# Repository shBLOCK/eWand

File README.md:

# ⚡eWand: a smart portable electrostatic charge generator

**This project is still highly WIP, as of right now, it does generate charge, but not much control is possible yet.**
<br>
This project is a group project, deriving from my school's project-based learning month.
<br>
Documentation is WIP.

## ⚙️Main features
- Portable
- Fully solid-state operation
- Precisely controllable output
- Output charge measurement (WIP)
- Wireless connectivity
  - Remote configuration & control
  - Data feedback

## Usages
- Physics teaching aid
- ESD testing
- ...

## Notes
- This project is inspired by [Join The Technicians's device](https://www.youtube.com/watch?v=TUDd5lzepgE), but adds more "smart" features to make it more useful as a teaching aid device and for other purposes.

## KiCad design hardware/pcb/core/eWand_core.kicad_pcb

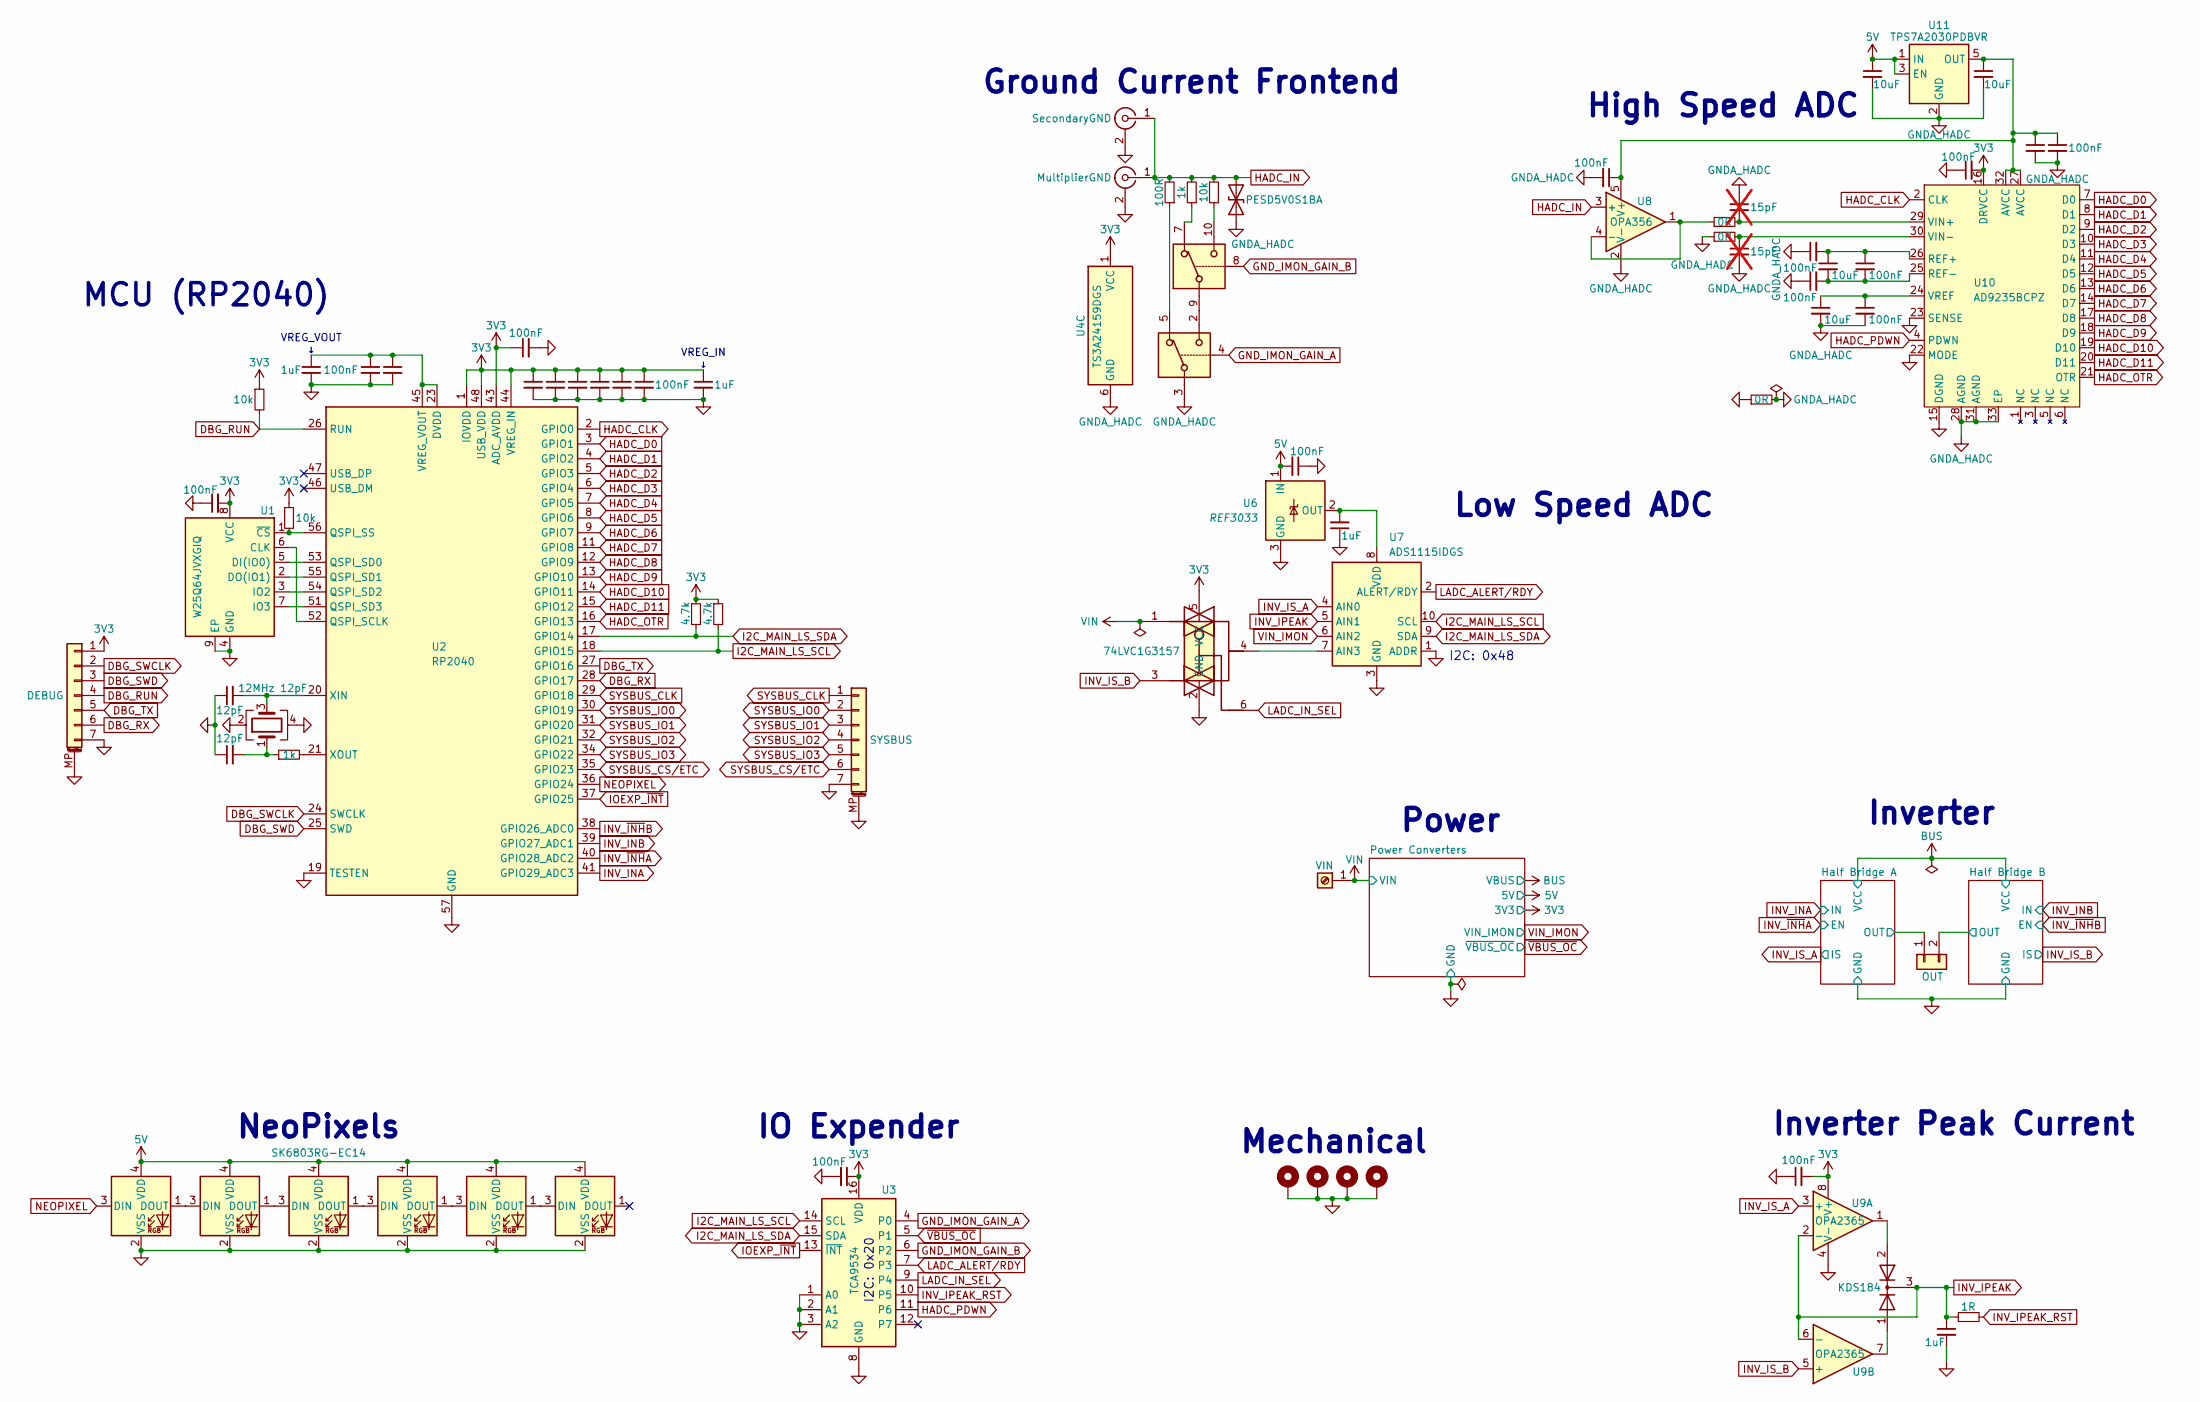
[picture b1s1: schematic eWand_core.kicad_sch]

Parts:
C1, C5, C6, C7, C8, C9, C10, C11, C12, C13, C15, C16, C18, C21, C22, C23, C26, C27, C30, C32, C33: 100nF; C_0402_1005Metric; LCSC C307331
C2, C3: 12pF; C_0402_1005Metric; LCSC C1547
C4, C14, C17: 1uF; C_0402_1005Metric; LCSC C52923
C19, C20: 15pF; C_0402_1005Metric; LCSC C1548; not fitted
C24, C25, C28, C31: 10uF; C_0402_1005Metric; LCSC C15525
C29: 1uF; C_0805_2012Metric; LCSC C28323
D1, D2, D3, D4, D5, D6: SK6803RG-EC14; LED_SK6812_EC15_1.5x1.5mm; LCSC C18548258
D7: PESD5V0S1BA; D_SOD-323; LCSC C19224
D8: KDS184; SOT-23; LCSC C112694
H1, H2, H3, H4: MountingHole_Pad; MountingHole_2.2mm_M2_Pad_Via
J1: DEBUG; TE_0-1734839-7_1x07-1MP_P0.5mm_Horizontal; LCSC C2911879
J2: SYSBUS; TE_0-1734839-7_1x07-1MP_P0.5mm_Horizontal; LCSC C262232
J3: SecondaryGND; U.FL_Molex_MCRF_73412-0110_Vertical; LCSC C411563
J4: MultiplierGND; U.FL_Molex_MCRF_73412-0110_Vertical; LCSC C411563
J5: VIN; T31000; LCSC C481468
J6: OUT; VH3.96-2AW; LCSC C722831
R1, R2: 10k; R_0402_1005Metric; LCSC C25744
R3: 1k; R_0402_1005Metric; LCSC C11702
R4, R5: 4.7k; R_0402_1005Metric; LCSC C25900
R6: 100R; C_0603_1608Metric; LCSC C22775
R7: 1k; C_0603_1608Metric; LCSC C21190
R8: 10k; C_0603_1608Metric; LCSC C25804
R9, R10: 0R; R_0402_1005Metric; LCSC C17168
R11: 0R; R_0603_1608Metric; LCSC C21189
R12: 1R; R_0402_1005Metric; LCSC C185446
U1: W25Q64JVXGIQ; WSON-8-1EP_4x4mm_P0.8mm_EP2.2x3mm; LCSC C2940195
U2: RP2040; QFN-56-1EP_7x7mm_P0.4mm_EP3.2x3.2mm; LCSC C2040
U3: TCA9534; TSSOP-16_4.4x5mm_P0.65mm; LCSC C206010
U4: TS3A24159DGS; TSSOP-10_3x3mm_P0.5mm; LCSC C129329
U5: 74LVC1G3157; SOT-363_SC-70-6; LCSC C38663
U6: REF3033; SOT-23; LCSC C36658
U7: ADS1115IDGS; TSSOP-10_3x3mm_P0.5mm; LCSC C37593
U8: OPA356; SOT-23-5; LCSC C183100
U9: OPA2365; SOIC-8_3.9x4.9mm_P1.27mm; LCSC C130011
U10: AD9235BCPZ; LFCSP-32-1EP_5x5mm_P0.5mm_EP3.1x3.1mm; LCSC C653330
U11: TPS7A2030PDBVR; SOT-23-5; LCSC C963429
Y1: 12MHz 12pF; Crystal_SMD_3225-4Pin_3.2x2.5mm; LCSC C70565

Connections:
3V3: C1.2, C7.1, C8.1, C9.1, C10.1, C11.1, C12.1, C13.1, C14.1, C15.1, C21.2, C30.2, J1.1, R1.1, R2.1, R4.1, R5.1, U1.8 (VCC), U2.1 (IOVDD), U2.10 (IOVDD), U2.22 (IOVDD), U2.33 (IOVDD), U2.42 (IOVDD), U2.43 (ADC_AVDD), U2.44 (VREG_IN), U2.48 (USB_VDD), U2.49 (IOVDD), U3.16 (VDD), U4.1 (VCC), U5.5 (VCC), U9.8 (V+), U10.16 (DRVCC); also elsewhere on the board
5V: C16.2, C28.1, D1.4 (VDD), D2.4 (VDD), D3.4 (VDD), D4.4 (VDD), D5.4 (VDD), D6.4 (VDD), U6.1 (IN), U11.1 (IN), U11.3 (EN); also elsewhere on the board
/Half Bridge A/OUT: J6.1; also elsewhere on the board
/Half Bridge B/OUT: J6.2; also elsewhere on the board
DBG_RUN: J1.4, R1.2, U2.26 (RUN)
DBG_RX: J1.6, U2.28 (GPIO17)
DBG_SWCLK: J1.2, U2.24 (SWCLK)
DBG_SWD: J1.3, U2.25 (SWD)
DBG_TX: J1.5, U2.27 (GPIO16)
GND: C1.1, C2.1, C3.1, C4.2, C5.2, C6.2, C7.2, C8.2, C9.2, C10.2, C11.2, C12.2, C13.2, C14.2, C15.2, C16.1, C17.1, C21.1, C29.2, C30.1, D1.2 (VSS), D2.2 (VSS), D3.2 (VSS), D4.2 (VSS), D5.2 (VSS), D6.2 (VSS), H1.1, H2.1, H3.1, H4.1, J1.7, J1.MP (MountPin), J2.7, J2.MP (MountPin), J3.2 (Ext), J4.2 (Ext), R11.1, U1.4 (GND), U1.9 (EP), U2.19 (TESTEN), U2.57 (GND), U3.1 (A0), U3.2 (A1), U3.3 (A2), U3.8 (GND), U5.2 (GND), U6.3 (GND), U7.1 (ADDR), U7.3 (GND), U9.4 (V-), U10.15 (DGND), U10.22 (MODE), U10.23 (SENSE), Y1.2, Y1.4; also elsewhere on the board
GNDA_HADC: C18.2, C19.1, C20.2, C22.1, C23.1, C24.2, C27.2, C28.2, C31.2, C32.2, C33.2, D7.1 (A1), R10.1, R11.2, U4.3, U4.6 (GND), U8.2 (V-), U10.28 (AGND), U10.31 (AGND), U10.33 (EP), U11.2 (GND)
GND_IMON_GAIN_A: U3.4 (P0), U4.4
GND_IMON_GAIN_B: U3.6 (P2), U4.8
HADC_CLK: U2.2 (GPIO0), U10.2 (CLK)
HADC_D0: U2.3 (GPIO1), U10.7 (D0)
HADC_D1: U2.4 (GPIO2), U10.8 (D1)
HADC_D2: U2.5 (GPIO3), U10.9 (D2)
HADC_D3: U2.6 (GPIO4), U10.10 (D3)
HADC_D4: U2.7 (GPIO5), U10.11 (D4)
HADC_D5: U2.8 (GPIO6), U10.12 (D5)
HADC_D6: U2.9 (GPIO7), U10.13 (D6)
HADC_D7: U2.11 (GPIO8), U10.14 (D7)
HADC_D8: U2.12 (GPIO9), U10.17 (D8)
HADC_D9: U2.13 (GPIO10), U10.18 (D9)
HADC_D10: U2.14 (GPIO11), U10.19 (D10)
HADC_D11: U2.15 (GPIO12), U10.20 (D11)
HADC_IN: D7.2 (A2), J3.1 (In), J4.1 (In), R6.2, R7.2, R8.2, U8.3 (+)
HADC_OTR: U2.16 (GPIO13), U10.21 (OTR)
HADC_PDWN: U3.11 (P6), U10.4 (PDWN)
I2C_MAIN_LS_SCL: R5.2, U2.18 (GPIO15), U3.14 (SCL), U7.10 (SCL); also elsewhere on the board
I2C_MAIN_LS_SDA: R4.2, U2.17 (GPIO14), U3.15 (SDA), U7.9 (SDA); also elsewhere on the board
INV_INA: U2.41 (GPIO29_ADC3); also elsewhere on the board
INV_INB: U2.39 (GPIO27_ADC1); also elsewhere on the board
INV_IPEAK: C29.1, D8.3 (K), R12.1, U7.5 (AIN1), U9.2 (-), U9.6 (-)
INV_IPEAK_RST: R12.2, U3.10 (P5)
INV_IS_A: U7.4 (AIN0), U9.3 (+); also elsewhere on the board
INV_IS_B: U5.3, U9.5 (+); also elsewhere on the board
INV_~INHA: U2.40 (GPIO28_ADC2); also elsewhere on the board
INV_~INHB: U2.38 (GPIO26_ADC0); also elsewhere on the board
IOEXP_~INT: U2.37 (GPIO25), U3.13 (~INT)
LADC_ALERT/RDY: U3.7 (P3), U7.2 (ALERT/RDY)
LADC_IN_SEL: U3.9 (P4), U5.6
NEOPIXEL: D1.3 (DIN), U2.36 (GPIO24)
unnamed: C3.2, R3.1, Y1.1
unnamed: D1.1 (DOUT), D2.3 (DIN)
unnamed: D2.1 (DOUT), D3.3 (DIN)
unnamed: D3.1 (DOUT), D4.3 (DIN)
unnamed: D4.1 (DOUT), D5.3 (DIN)
unnamed: D5.1 (DOUT), D6.3 (DIN)
unnamed: D8.1 (A), U9.7
unnamed: D8.2 (A), U9.1
unnamed: R6.1, U4.5
unnamed: R7.1, U4.7
unnamed: R8.1, U4.10
unnamed: U1.6 (CLK), U2.52 (QSPI_SCLK)
unnamed: U1.5 (DI(IO0)), U2.53 (QSPI_SD0)
unnamed: U1.2 (DO(IO1)), U2.55 (QSPI_SD1)
unnamed: U1.3 (IO2), U2.54 (QSPI_SD2)
unnamed: U1.7 (IO3), U2.51 (QSPI_SD3)
unnamed: R2.2, U1.1 (~CS), U2.56 (QSPI_SS)
unnamed: C4.1, C5.1, C6.1, U2.23 (DVDD), U2.45 (VREG_VOUT), U2.50 (DVDD)
unnamed: C2.2, U2.20 (XIN), Y1.3
unnamed: R3.2, U2.21 (XOUT)
unnamed: U4.2, U4.9
unnamed: C17.2, U6.2 (OUT), U7.8 (VDD)
unnamed: U5.4, U7.7 (AIN3)
unnamed: R9.1, U8.1, U8.4 (-)
unnamed: C22.2, C25.1, C26.1, U10.26 (REF+)
unnamed: C23.2, C25.2, C26.2, U10.25 (REF-)
unnamed: C19.2, R9.2, U10.29 (VIN+)
unnamed: C20.1, R10.2, U10.30 (VIN-)
unnamed: C24.1, C27.1, U10.24 (VREF)
unnamed: C18.1, C31.1, C32.1, C33.1, U8.5 (V+), U10.27 (AVCC), U10.32 (AVCC), U11.5 (OUT)
SYSBUS_CLK: J2.1, U2.29 (GPIO18)
SYSBUS_CS/ETC: J2.6, U2.35 (GPIO23)
SYSBUS_IO0: J2.2, U2.30 (GPIO19)
SYSBUS_IO1: J2.3, U2.31 (GPIO20)
SYSBUS_IO2: J2.4, U2.32 (GPIO21)
SYSBUS_IO3: J2.5, U2.34 (GPIO22)
VIN: J5.1, U5.1; also elsewhere on the board
VIN_IMON: U7.6 (AIN2); also elsewhere on the board
~VBUS_OC: U3.5 (P1); also elsewhere on the board

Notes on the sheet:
Inverter Peak Current
High Speed ADC
Ground Current Frontend
Inverter
Power
VREG_IN ↓
VREG_VOUT ↓
Low Speed ADC
I2C: 0x20
IO Expender
Mechanical
NeoPixels
I2C: 0x48
MCU (RP2040)

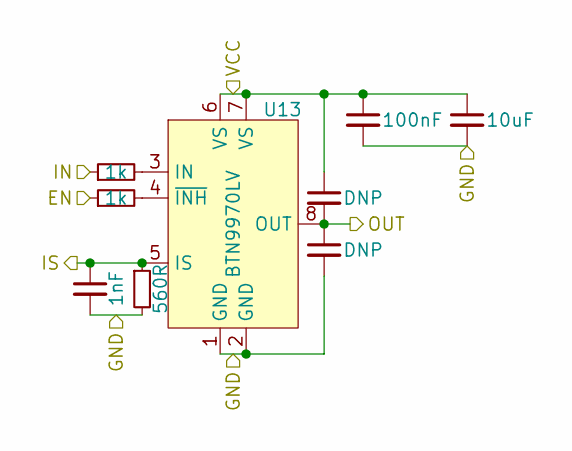
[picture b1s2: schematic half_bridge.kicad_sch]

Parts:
C39: 1nF; C_0402_1005Metric; LCSC C1523
C40, C41: DNP; C_0805_2012Metric
C42: 100nF; C_0402_1005Metric; LCSC C307331
C43: 10uF; C_1206_3216Metric; LCSC C13585
R16, R17: 1k; R_0402_1005Metric; LCSC C11702
R18: 560R; R_0402_1005Metric; LCSC C25126
U13: BTN9970LV; PG-HSOF-7-1; LCSC C3655537

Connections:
/Half Bridge B/OUT: C40.2, C41.1, U13.8 (OUT); also elsewhere on the board
BUS: C40.1, C42.1, C43.1, U13.6 (VS), U13.7 (VS); also elsewhere on the board
GND: C39.2, C41.2, C42.2, C43.2, R18.2, U13.1 (GND), U13.2 (GND); also elsewhere on the board
INV_INB: R16.1; also elsewhere on the board
INV_IS_B: C39.1, R18.1, U13.5 (IS); also elsewhere on the board
INV_~INHB: R17.1; also elsewhere on the board
unnamed: R16.2, U13.3 (IN)
unnamed: R17.2, U13.4 (~INH)

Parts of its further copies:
C34: 1nF; C_0402_1005Metric; LCSC C1523
C35, C36: DNP; C_0805_2012Metric
C37: 100nF; C_0402_1005Metric; LCSC C307331
C38: 10uF; C_1206_3216Metric; LCSC C13585
R13, R14: 1k; R_0402_1005Metric; LCSC C11702
R15: 560R; R_0402_1005Metric; LCSC C25126
U12: BTN9970LV; PG-HSOF-7-1; LCSC C3655537

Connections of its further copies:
/Half Bridge A/OUT: C35.2, C36.1, U12.8 (OUT); also elsewhere on the board
BUS: C35.1, C37.1, C38.1, U12.6 (VS), U12.7 (VS); also elsewhere on the board
GND: C34.2, C36.2, C37.2, C38.2, R15.2, U12.1 (GND), U12.2 (GND); also elsewhere on the board
INV_INA: R13.1; also elsewhere on the board
INV_IS_A: C34.1, R15.1, U12.5 (IS); also elsewhere on the board
INV_~INHA: R14.1; also elsewhere on the board
unnamed: R13.2, U12.3 (IN)
unnamed: R14.2, U12.4 (~INH)

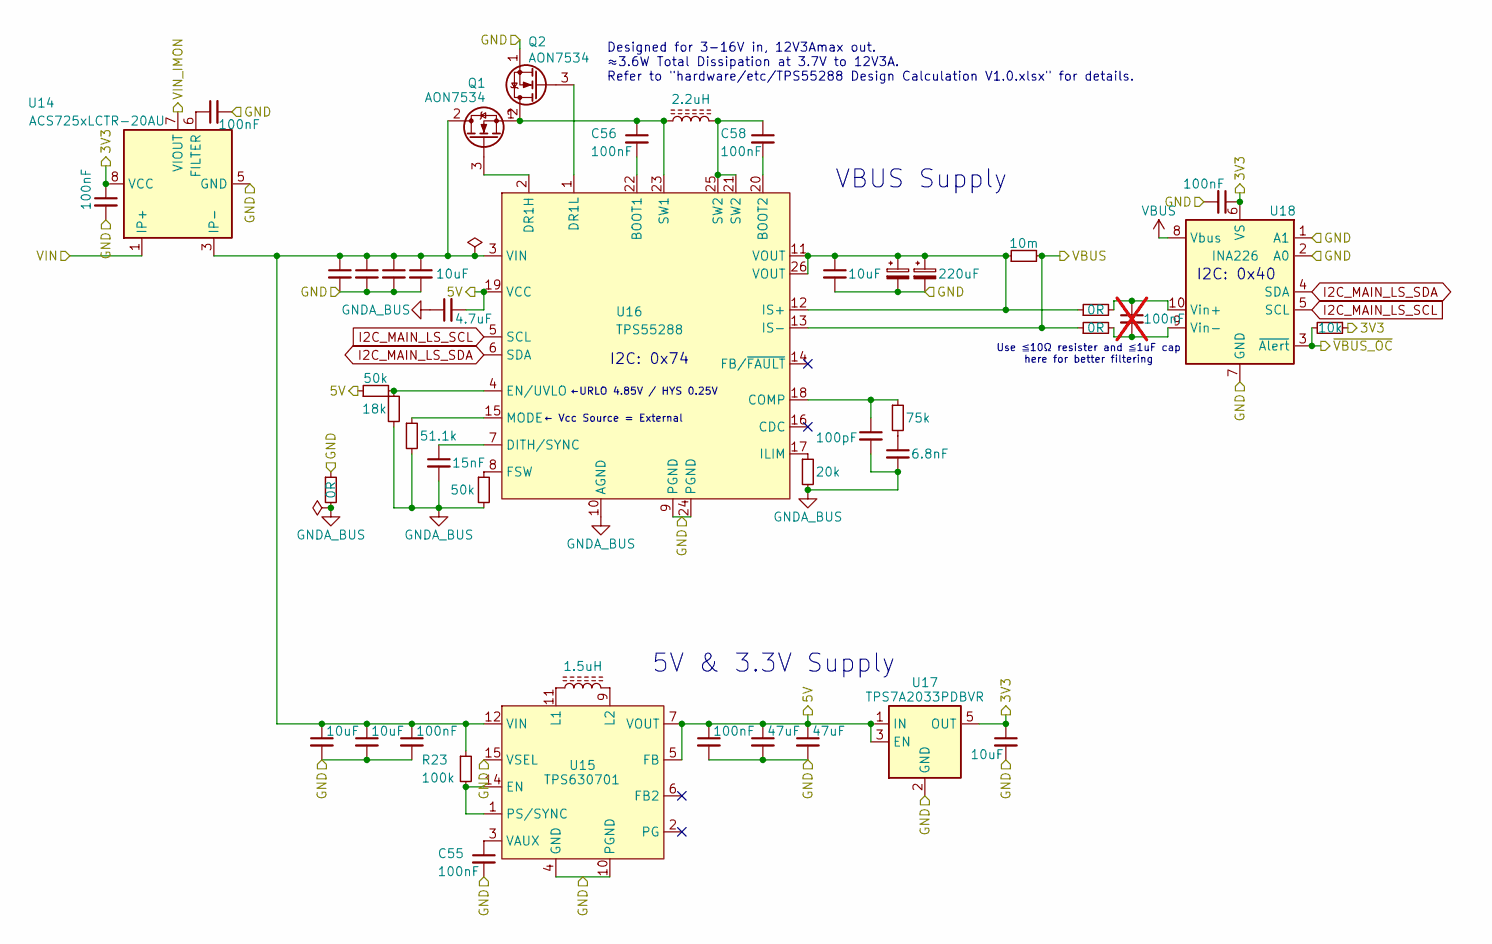
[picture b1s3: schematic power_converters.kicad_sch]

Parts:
C44, C45, C51, C55, C56, C57, C58, C68: 100nF; C_0402_1005Metric; LCSC C307331
C46, C47, C48, C49, C50, C52: 10uF; C_0805_2012Metric; LCSC C15850
C53: 15nF; C_0402_1005Metric; LCSC C114405
C54: 4.7uF; C_0402_1005Metric; LCSC C318563
C59, C60: 47uF; C_0805_2012Metric; LCSC C16780
C61: 10uF; C_1206_3216Metric; LCSC C13585
C62: 100pF; C_0402_1005Metric; LCSC C1546
C63: 220uF; CP_Radial_D6.3mm_P2.50mm_L8mm_Horizontal; LCSC C2943986
C64: 6.8nF; C_0402_1005Metric; LCSC C1542
C65: 220uF; CP_Radial_D6.3mm_P2.50mm_L8mm_Horizontal_Fli; LCSC C2943986
C66: 10uF; C_0402_1005Metric; LCSC C15525
C67: 100nF; C_0402_1005Metric; LCSC C307331; not fitted
L1: 1.5uH; L_Changjiang_FNR252012S; LCSC C5832371
L2: 2.2uH; L_Coilcraft_XAL1010-XXX; LCSC C5125746
Q1, Q2: AON7534; DFN-8_3x3; LCSC C115844
R19: 0R; R_0603_1608Metric; LCSC C21189
R20, R24: 50k; R_0402_1005Metric; LCSC C166559
R21: 18k; R_0402_1005Metric; LCSC C25762
R22: 51.1k; R_0402_1005Metric; LCSC C284602
R23: 100k; R_0402_1005Metric; LCSC C25741
R25: 20k; R_0402_1005Metric; LCSC C25765
R26: 75k; R_0402_1005Metric; LCSC C25798
R27: 10m; R_1206_3216Metric; LCSC C2961483
R28, R29: 0R; R_0402_1005Metric; LCSC C17168
R30: 10k; R_0402_1005Metric; LCSC C25744
U14: ACS725xLCTR-20AU; SOIC-8_3.9x4.9mm_P1.27mm; LCSC C459335
U15: TPS630701; VQFN-HR-15; LCSC C2876599
U16: TPS55288; RPM0026A-MFG; LCSC C2876595
U17: TPS7A2033PDBVR; SOT-23-5; LCSC C2862740
U18: INA226; VSSOP-10_3x3mm_P0.5mm; LCSC C49851

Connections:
3V3: C44.1, C66.1, C68.1, R30.1, U14.8 (VCC), U17.5 (OUT), U18.6 (VS); also elsewhere on the board
5V: C54.2, C57.1, C59.1, C60.1, R20.1, U15.5 (FB), U15.7 (VOUT), U16.19 (VCC), U17.1 (IN), U17.3 (EN); also elsewhere on the board
BUS: R27.2, R29.1, U16.13 (IS-), U18.8 (Vbus); also elsewhere on the board
GND: C44.2, C45.2, C46.2, C47.2, C48.2, C49.2, C50.2, C51.2, C52.2, C55.2, C57.2, C59.2, C60.2, C61.2, C63.2, C65.2, C66.2, C68.2, Q2.1 (S), R19.1, U14.5 (GND), U15.4 (GND), U15.10 (PGND), U15.15 (VSEL), U16.9 (PGND), U16.24 (PGND), U17.2 (GND), U18.1 (A1), U18.2 (A0), U18.7 (GND); also elsewhere on the board
GNDA_BUS: C53.2, C54.1, C62.2, C64.2, R19.2, R21.2, R22.2, R24.2, R25.2, U16.10 (AGND)
I2C_MAIN_LS_SCL: U16.5 (SCL), U18.5 (SCL); also elsewhere on the board
I2C_MAIN_LS_SDA: U16.6 (SDA), U18.4 (SDA); also elsewhere on the board
unnamed: C58.1, L2.2, U16.21 (SW2), U16.25 (SW2)
unnamed: C64.1, R26.2
unnamed: C46.1, C47.1, C48.1, C49.1, C50.1, C51.1, C52.1, Q1.2 (D), R23.1, U14.3 (IP-), U14.4 (IP-), U15.12 (VIN), U16.3 (VIN)
unnamed: Q1.3 (G), U16.2 (DR1H)
unnamed: C56.1, L2.1, Q1.1 (S), Q2.2 (D), U16.23 (SW1)
unnamed: Q2.3 (G), U16.1 (DR1L)
unnamed: C45.1, U14.6 (FILTER)
unnamed: R23.2, U15.1 (PS/SYNC), U15.14 (EN)
unnamed: L1.1, U15.11 (L1)
unnamed: L1.2, U15.9 (L2)
unnamed: C55.1, U15.3 (VAUX)
unnamed: C56.2, U16.22 (BOOT1)
unnamed: C58.2, U16.20 (BOOT2)
unnamed: C62.1, R26.1, U16.18 (COMP)
unnamed: C53.1, U16.7 (DITH/SYNC)
unnamed: R20.2, R21.1, U16.4 (EN/UVLO)
unnamed: R24.1, U16.8 (FSW)
unnamed: R25.1, U16.17 (ILIM)
unnamed: C61.1, C63.1, C65.1, R27.1, R28.1, U16.11 (VOUT), U16.12 (IS+), U16.26 (VOUT)
unnamed: R22.1, U16.15 (MODE)
unnamed: C67.1, R28.2, U18.10 (Vin+)
unnamed: C67.2, R29.2, U18.9 (Vin-)
VIN: U14.1 (IP+), U14.2 (IP+); also elsewhere on the board
VIN_IMON: U14.7 (VIOUT); also elsewhere on the board
~VBUS_OC: R30.2, U18.3 (~Alert); also elsewhere on the board

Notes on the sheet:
Use ≦10Ω resister and ≦1uF cap here for better filtering
5V & 3.3V Supply
I2C: 0x74
Designed for 3-16V in, 12V3Amax out. ≈3.6W Total Dissipation at 3.7V to 12V3A. Refer to "hardware/etc/TPS55288 Design Calculation V1.0.xlsx" for details.
←URLO 4.85V / HYS 0.25V
← Vcc Source = External
VBUS Supply
I2C: 0x40

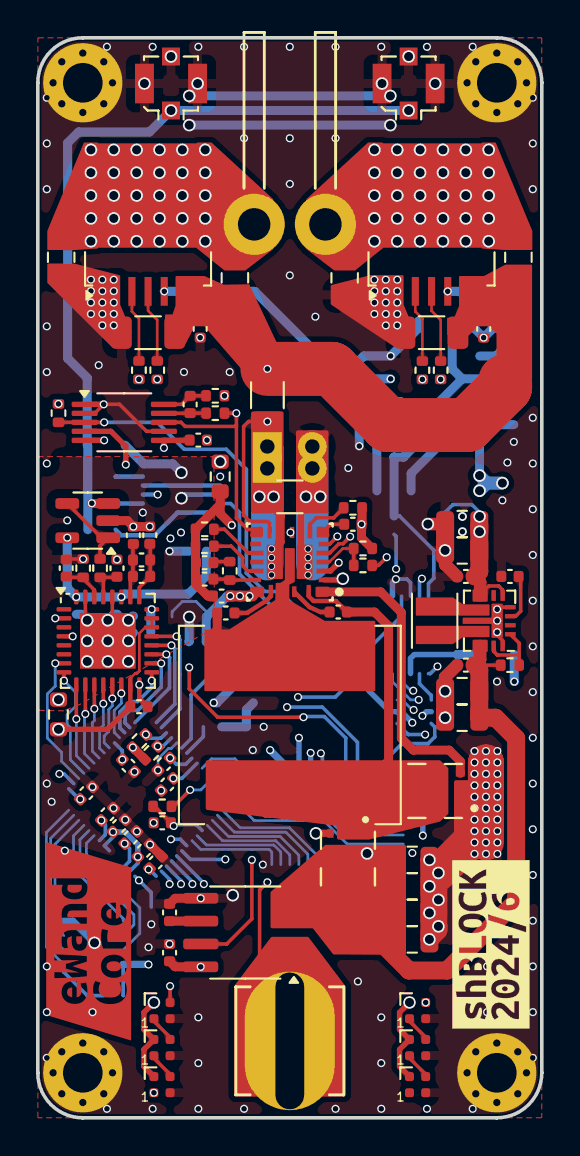
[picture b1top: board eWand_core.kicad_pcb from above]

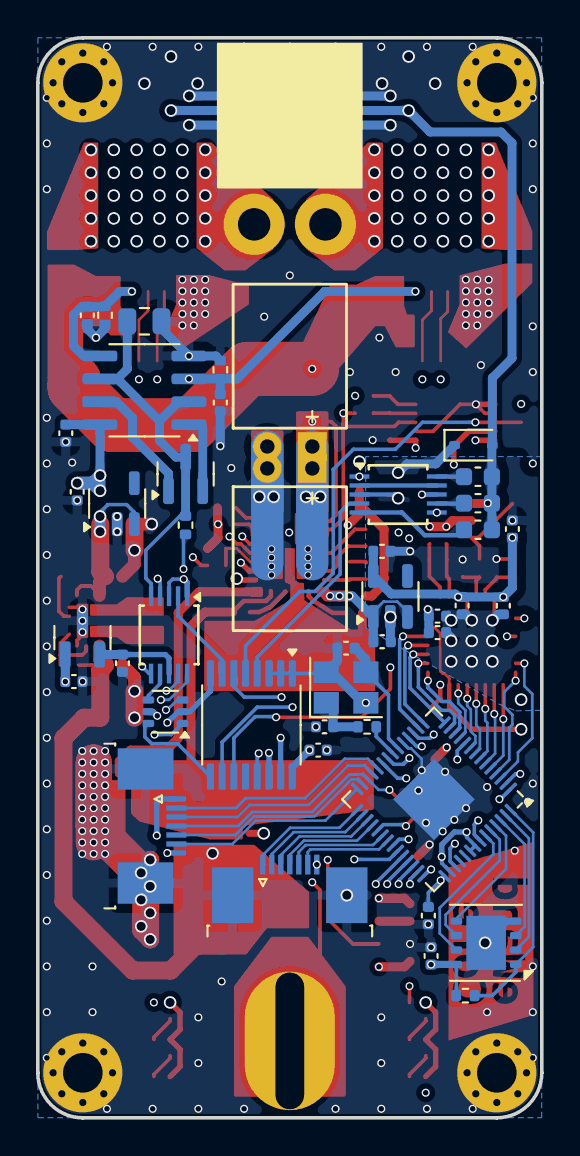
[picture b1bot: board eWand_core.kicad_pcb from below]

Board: 6 copper layers, 28.0 x 60.0 mm, 141 parts (44 on the bottom side), 110 nets.

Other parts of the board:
kibuzzard-6674E35D: G***; kibuzzard-6674E35D
kibuzzard-66739BFE: G***; kibuzzard-66739BFE

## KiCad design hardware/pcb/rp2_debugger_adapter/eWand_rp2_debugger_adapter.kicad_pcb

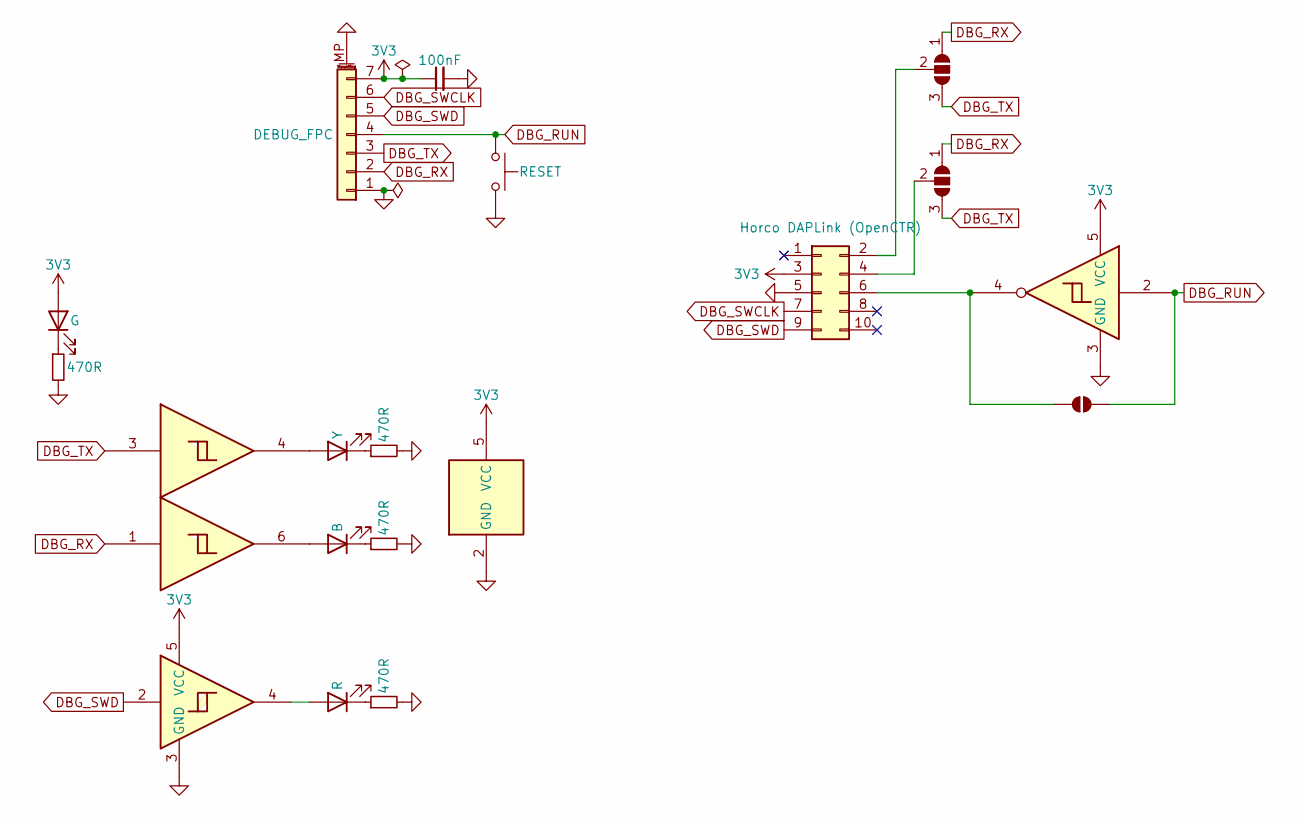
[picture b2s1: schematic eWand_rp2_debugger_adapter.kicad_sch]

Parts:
C1: 100nF; C_0402_1005Metric; LCSC C307331
D1: R; LED_0603_1608Metric; LCSC C84263
D2: Y; LED_0603_1608Metric; LCSC C84268
D3: B; LED_0603_1608Metric; LCSC C84266
D4: G; LED_0603_1608Metric; LCSC C84267
J1: DEBUG_FPC; TE_0-1734839-7_1x07-1MP_P0.5mm_Horizontal; LCSC C2911968
J2: Horco DAPLink (OpenCTR); PinSocket_2x05_P2.54mm_Horizontal; LCSC C2897425
JP1, JP2: SolderJumper_3_Open; SolderJumper-3_P1.3mm_Open_RoundedPad1.0x1.5mm
JP3: SolderJumper_2_Open; SolderJumper-2_P1.3mm_Open_RoundedPad1.0x1.5mm
R1, R2, R3, R4: 470R; R_0603_1608Metric; LCSC C23179
SW1: RESET; SW_SPST_CK_RS282G05A3; LCSC C318938
U1: SN74LVC1G14DBV; SOT-23-5; LCSC C7835
U2: 74LVC2G17; SOT-23-6; LCSC C10429
U4: 74LVC1G17; SOT-23-5; LCSC C7836

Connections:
3V3: C1.1, D4.2 (A), J1.7, J2.3, U1.5 (VCC), U2.5 (VCC), U4.5 (VCC)
DBG_RUN: J1.4, JP3.2 (B), SW1.1, U1.2
DBG_RX: J1.2, JP1.1 (A), JP2.1 (A), U2.1
DBG_SWCLK: J1.6, J2.7
DBG_SWD: J1.5, J2.9, U4.2
DBG_TX: J1.3, JP1.3 (B), JP2.3 (B), U2.3
GND: C1.2, J1.1, J1.MP (MountPin), J2.5, R1.2, R2.2, R3.2, R4.2, SW1.2, U1.3 (GND), U2.2 (GND), U4.3 (GND)
unnamed: D1.2 (A), U4.4
unnamed: D1.1 (K), R1.1
unnamed: D2.2 (A), U2.4
unnamed: D2.1 (K), R2.1
unnamed: D3.2 (A), U2.6
unnamed: D3.1 (K), R3.1
unnamed: D4.1 (K), R4.1
unnamed: J2.2, JP1.2 (C)
unnamed: J2.4, JP2.2 (C)
unnamed: J2.6, JP3.1 (A), U1.4

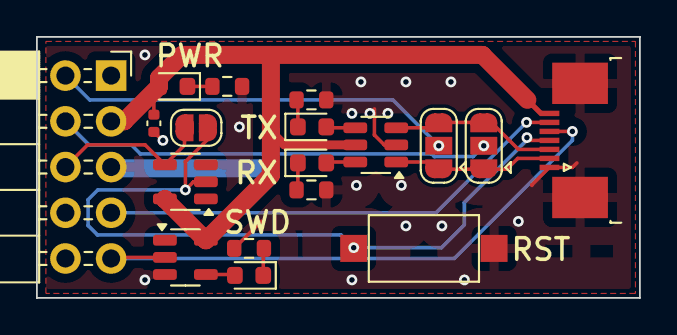
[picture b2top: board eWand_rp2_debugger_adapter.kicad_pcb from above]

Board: 2 copper layers, 33.5 x 14.5 mm, 18 parts (0 on the bottom side), 17 nets.

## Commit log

2024-06-24 Save old progress before switching to using PWM instead of PIO for power stage.
2024-06-29 utils.h
2024-06-29 clion files
2024-06-29 neopixel
2024-06-29 I2C Bus IO Expander
2024-06-29 Update pcb
2024-06-29 High speed ADC initial version (not validated)
2024-06-29 Use #pragma once
2024-06-29 Project file templates
2024-06-29 git_toolbox_prj.xml
2024-06-30 Power stage PWM implementation
2024-06-30 TPS55288 DCDC implementation
2024-06-30 Fix IO expander
2024-06-30 I2C bus 16bit operations
2024-10-14 Upload current progress (see detailed message), development is pause for now...
